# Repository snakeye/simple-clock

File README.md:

# simple-clock
Simple 7 Segment clock

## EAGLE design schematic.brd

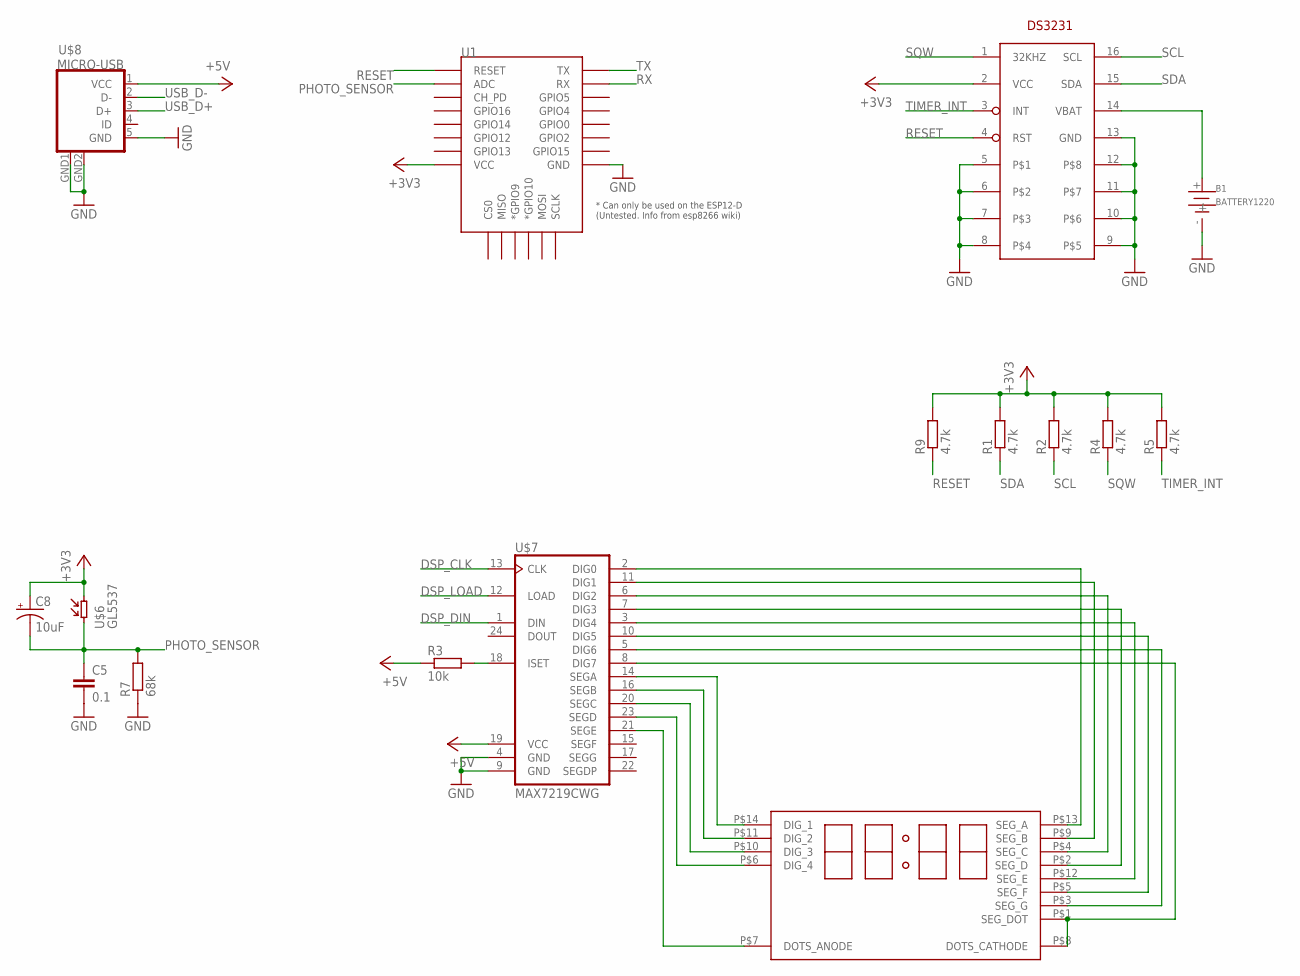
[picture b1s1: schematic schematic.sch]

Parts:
B1: BATTERY1220; 1220-SMD
C5: 0.1; C0805
C8: 10uF; EIA3216
R1, R2, R4, R5, R9: 4.7k; R0805
R3: 10k; R0805
R7: 68k; R0805
U1: ESP12ESMD; ESP12E-SMD
U$1: LBT8402BW; LBT8402
U$2: DS3231WIDE; SO16W
U$6: GL5537; GL55
U$7: MAX7219CWG; SO24L
U$8: MICRO-USB

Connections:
+3V3: C8.A (+), R1.2, R2.2, R4.2, R5.2, R9.2, U1.VCC, U$2.2 (VCC), U$6.P$2
+5V: R3.1, U$7.19 (VCC), U$8.1 (VCC)
DIG_1: U$1.P$14 (DIG_1), U$7.14 (SEGA)
DSP_CLK: U$7.13 (CLK)
DSP_DIN: U$7.1 (DIN)
DSP_LOAD: U$7.12 (LOAD)
GND: B1.-, C5.2, R7.1, U1.GND, U$2.5, U$2.6, U$2.7, U$2.8, U$2.9, U$2.10, U$2.11, U$2.12, U$2.13 (GND), U$7.4 (GND), U$7.9 (GND), U$8.5 (GND), U$8.GND1 (GND), U$8.GND2 (GND)
unnamed: R3.2, U$7.18 (ISET)
unnamed: U$1.P$11 (DIG_2), U$7.16 (SEGB)
unnamed: U$1.P$10 (DIG_3), U$7.20 (SEGC)
unnamed: U$1.P$6 (DIG_4), U$7.23 (SEGD)
unnamed: U$1.P$7 (DOTS_ANODE), U$7.21 (SEGE)
unnamed: U$1.P$13 (SEG_A), U$7.2 (DIG0)
unnamed: U$1.P$9 (SEG_B), U$7.11 (DIG1)
unnamed: U$1.P$4 (SEG_C), U$7.6 (DIG2)
unnamed: U$1.P$2 (SEG_D), U$7.7 (DIG3)
unnamed: U$1.P$12 (SEG_E), U$7.3 (DIG4)
unnamed: U$1.P$5 (SEG_F), U$7.10 (DIG5)
unnamed: U$1.P$3 (SEG_G), U$7.5 (DIG6)
unnamed: U$1.P$1 (SEG_DOT), U$1.P$8 (DOTS_CATHODE), U$7.8 (DIG7)
unnamed: B1.+, U$2.14 (VBAT)
PHOTO_SENSOR: C5.1, C8.C (-), R7.2, U1.ADC, U$6.P$1
RESET: R9.1, U1.RESET, U$2.4 (RST)
RX: U1.RXD0 (RX)
SCL: R2.1, U$2.16 (SCL)
SDA: R1.1, U$2.15 (SDA)
SQW: R4.1, U$2.1 (32KHZ)
TIMER_INT: R5.1, U$2.3 (INT)
TX: U1.TXD0 (TX)
USB_D+: U$8.3 (D+)
USB_D-: U$8.2 (D-)

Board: 2 copper layers, 16 parts (13 on the bottom side), 24 nets, no tracks yet.

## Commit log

2015-12-23 Added LED and STM32
2015-12-29 Element placement
2015-12-29 PCB v1
2016-01-03 PCB design
2016-02-20 Created AtmelStudio project
2016-02-20 Added .gitignore
2016-02-20 Added i2c and max7219 libraries
2016-02-20 Added schematic images and gerber files
2016-02-20 Display numbers
2016-02-21 Separated display functions
2016-02-21 Read data from DS3231 RTC
2016-03-13 Automatic brightness
2016-03-13 Moved brightness measurement to separate file
2016-10-18 Switched to Studio 7
2016-12-25 Handle buttons
2016-12-26 working version
2022-01-12 Added BOM file

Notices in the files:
parts and their libraries:
SparkFun-Capacitors: Licensing: Creative Commons ShareAlike 4.0 International - https://creativecommons.org/licenses/by-sa/4.0
